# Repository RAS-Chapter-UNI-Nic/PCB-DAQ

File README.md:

# PCB-DAQ
Taller de Fabricación de Circuitos impresos para los chicos de RAS.
Febrero 2019

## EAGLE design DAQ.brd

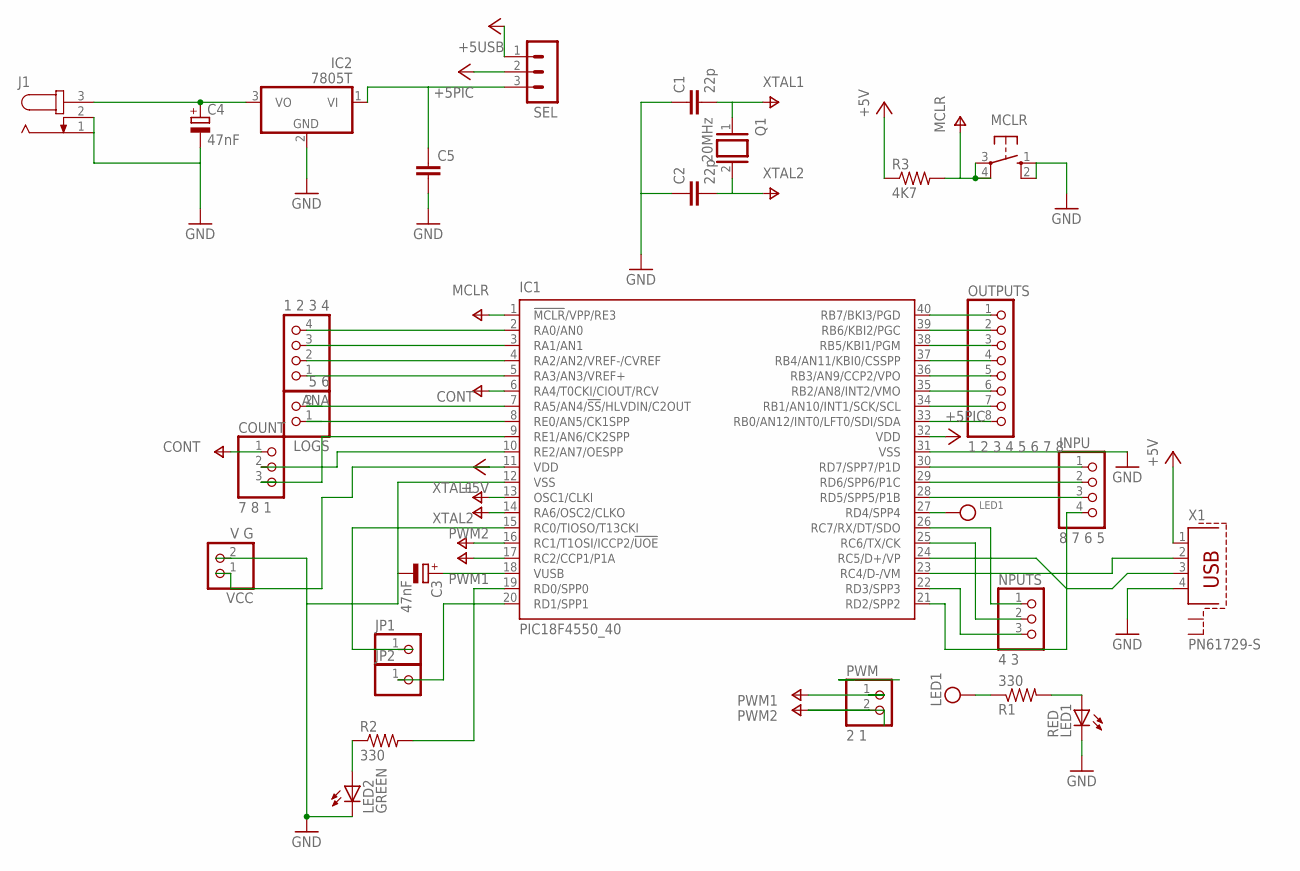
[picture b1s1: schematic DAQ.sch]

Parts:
ANA: 1 2 3 4; 1X04
C1, C2: 22p; C025-024X044
C3, C4: 47nF; E2,5-6E
C5: C-EU050-035X075; C050-035X075
COUNT: 7 8 1; 1X03
IC1: PIC18F4550_40; DIL40
IC2: 7805T; TO220H
INPU: 8 7 6 5; 1X04
J1: JACK-PLUG0; SPC4077
JP1, JP2: PINHD-1X1; 1X01
LED1: RED; LED3MM
LED2: GREEN; LED3MM
LOGS: 5 6; 1X02
MCLR: 10-XX; B3F-10XX
NPUTS: 4 3; 1X03
OUTPUTS: 1 2 3 4 5 6 7 8; 1X08
PWM: 2 1; 1X02
Q1: 20MHz; QS
R1, R2: 330; 0207/10
R3: 4K7; 0207/10
SEL: MA03-1
VCC: V G; 1X02
X1: PN61729-S

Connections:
+5PIC: IC1.11 (VDD), IC1.32 (VDD), R3.1, SEL.2, VCC.1
+5USB: SEL.1, X1.1
GND: C1.1, C2.1, C3.-, C4.-, C5.2, IC1.12 (VSS), IC1.31 (VSS), IC2.2 (GND), J1.1, J1.2, LED1.K (C), LED2.K (C), MCLR.1 (S), MCLR.2 (S1), VCC.2, X1.4
MCLR: IC1.1 (!MCLR!/VPP/RE3), MCLR.3, MCLR.4 (P1), R3.2
unnamed: IC1.23 (RC4/D-/VM), X1.2
unnamed: IC1.30 (RD7/SPP7/P1D), INPU.1
unnamed: IC1.40 (RB7/BKI3/PGD), OUTPUTS.1
unnamed: LED2.A, R2.1
unnamed: IC1.25 (RC6/TX/CK), NPUTS.2
unnamed: LED1.A, R1.2
unnamed: IC1.39 (RB6/KBI2/PGC), OUTPUTS.2
unnamed: IC1.38 (RB5/KBI1/PGM), OUTPUTS.3
unnamed: IC1.37 (RB4/AN11/KBI0/CSSPP), OUTPUTS.4
unnamed: IC1.36 (RB3/AN9/CCP2/VPO), OUTPUTS.5
unnamed: IC1.35 (RB2/AN8/INT2/VMO), OUTPUTS.6
unnamed: IC1.34 (RB1/AN10/INT1/SCK/SCL), OUTPUTS.7
unnamed: IC1.33 (RB0/AN12/INT0/LFT0/SDI/SDA), OUTPUTS.8
unnamed: IC1.24 (RC5/D+/VP), X1.3
unnamed: IC1.29 (RD6/SPP6/P1C), INPU.2
unnamed: IC1.28 (RD5/SPP5/P1B), INPU.3
unnamed: IC1.22 (RD3/SPP3), NPUTS.3
unnamed: IC1.15 (RC0/TIOSO/T13CKI), JP1.1
unnamed: C3.+, IC1.18 (VUSB)
unnamed: IC1.21 (RD2/SPP2), INPU.4
unnamed: IC1.19 (RD0/SPP0), R2.2
unnamed: ANA.4, IC1.2 (RA0/AN0)
unnamed: ANA.3, IC1.3 (RA1/AN1)
unnamed: ANA.2, IC1.4 (RA2/AN2/VREF-/CVREF)
unnamed: ANA.1, IC1.5 (RA3/AN3/VREF+)
unnamed: IC1.7 (RA5/AN4/!SS!/HLVDIN/C2OUT), LOGS.2
unnamed: IC1.8 (RE0/AN5/CK1SPP), LOGS.1
unnamed: IC1.20 (RD1/SPP1), JP2.1
unnamed 33: COUNT.3, IC1.9 (RE1/AN6/CK2SPP); also elsewhere on the board
unnamed 34: COUNT.2, IC1.10 (RE2/AN7/OESPP); also elsewhere on the board
unnamed: C4.+, IC2.3 (VO), J1.3
unnamed: C5.1, IC2.1 (VI), SEL.3
unnamed: IC1.26 (RC7/RX/DT/SDO), NPUTS.1
PWM1: IC1.17 (RC2/CCP1/P1A), PWM.1
PWM2: IC1.16 (RC1/T1OSI/ICCP2/!UOE), PWM.2
XTAL1: C1.2, IC1.13 (OSC1/CLKI), Q1.1
XTAL2: C2.2, IC1.14 (RA6/OSC2/CLKO), Q1.2

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
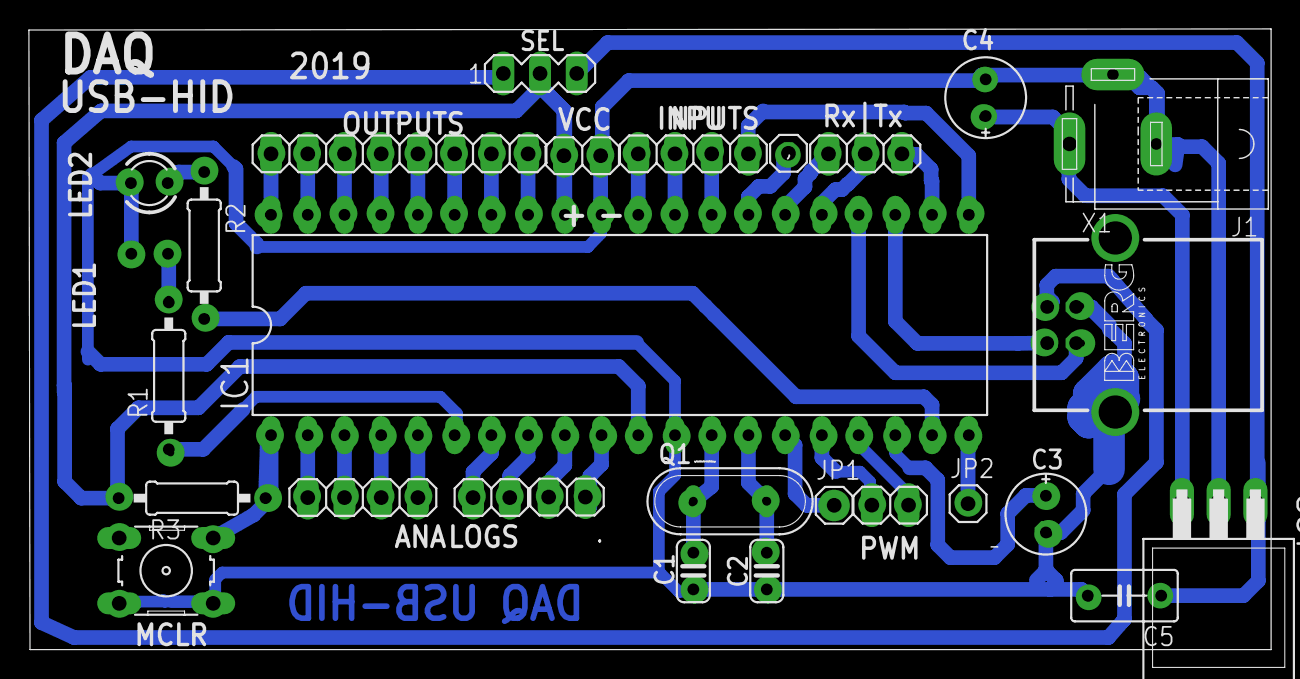
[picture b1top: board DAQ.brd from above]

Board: 2 copper layers, 85.9 x 42.9 mm, 28 parts (1 on the bottom side), 43 nets.

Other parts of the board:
,: 1X01
.: 7 8; 1X02

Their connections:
unnamed 33: ..2; also elsewhere on the board
unnamed 34: ..1; also elsewhere on the board

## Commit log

2018-12-17 List Components
2018-12-18 list full
2019-03-26 print doc
2019-06-15 Final
2019-06-18 Clase #2
2019-06-22 CAMotics
2019-06-26 files word
